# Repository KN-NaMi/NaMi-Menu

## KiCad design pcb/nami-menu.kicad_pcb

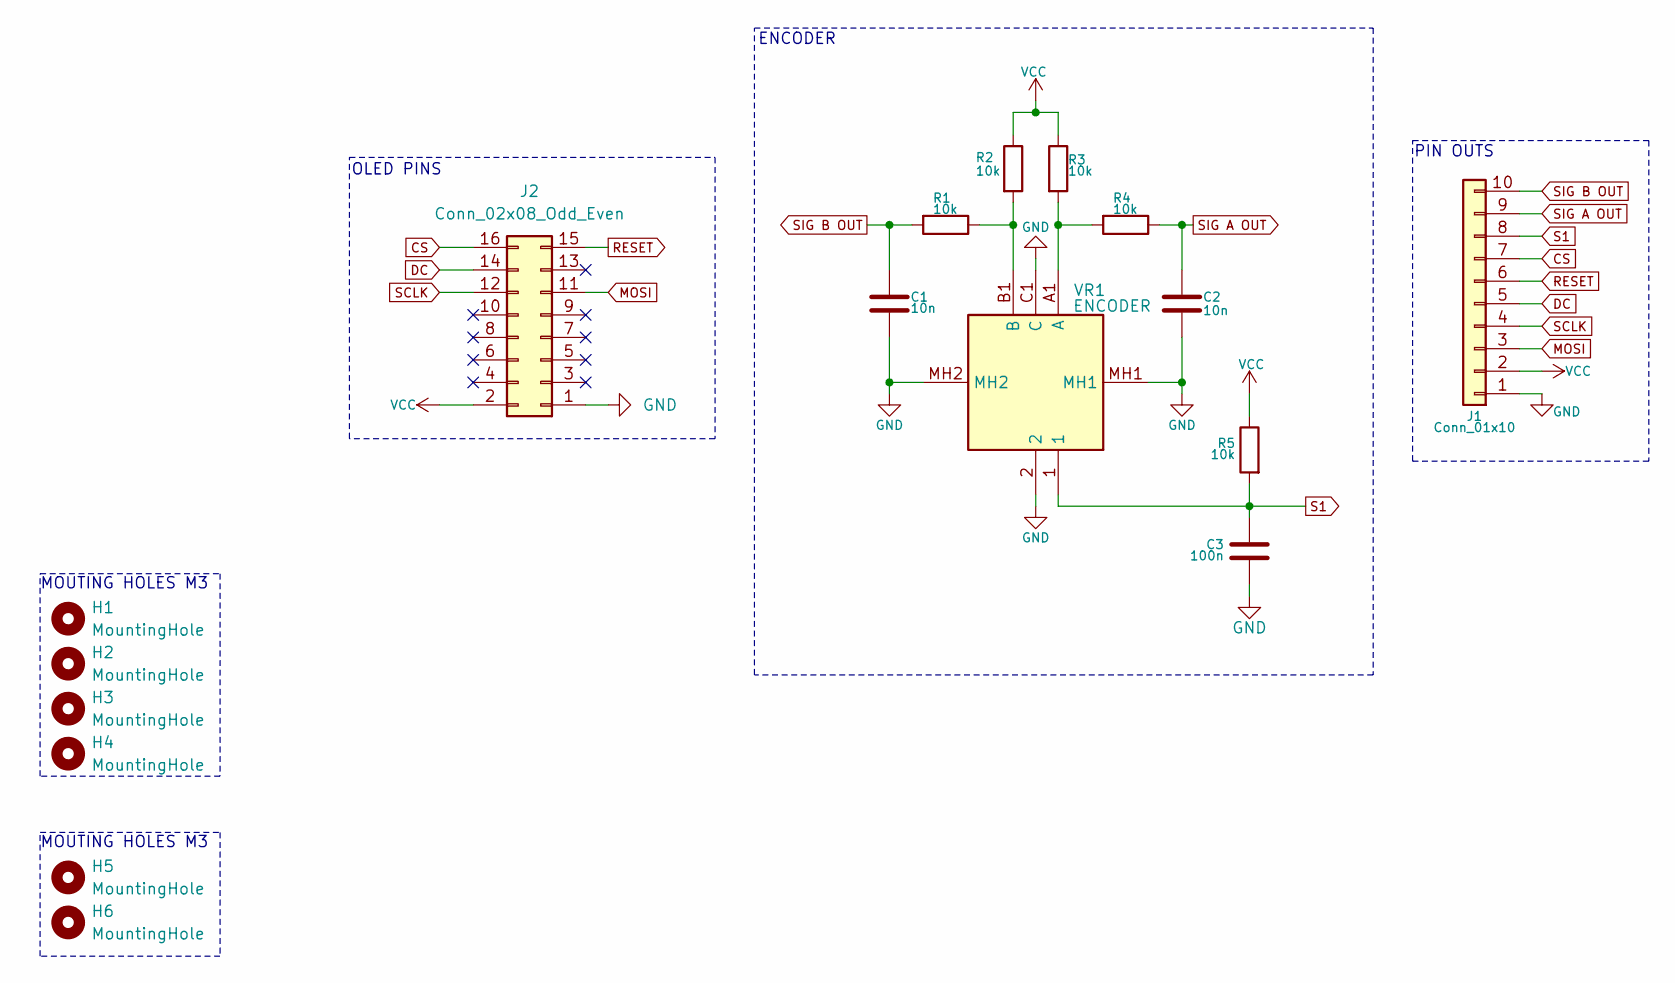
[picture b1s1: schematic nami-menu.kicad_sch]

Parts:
C1, C2: 10n; C_0402_1005Metric
C3: 100n; C_0402_1005Metric
H1, H2, H3, H4, H5, H6: MountingHole; MountingHole_3.2mm_M3
J1: Conn_01x10; PinHeader_1x10_P2.00mm_Vertical
J2: Conn_02x08_Odd_Even; PinSocket_2x08_P2.54mm_Vertical
R1, R2, R3, R4, R5: 10k; R_0402_1005Metric
VR1: ENCODER; PEC11R4220FS0024; Mouser Part Number 652-PEC11R-4220F-S24

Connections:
CS: J1.7, J2.16
DC: J1.5, J2.14
GND: C1.2, C2.2, C3.2, J1.1, J2.1, VR1.2, VR1.C1 (C), VR1.MH1, VR1.MH2
MOSI: J1.3, J2.11
unnamed: R3.2, R4.2, VR1.A1 (A)
unnamed: R1.1, R2.2, VR1.B1 (B)
RESET: J1.6, J2.15
S1: C3.1, J1.8, R5.2, VR1.1
SCLK: J1.4, J2.12
SIG A OUT: C2.1, J1.9, R4.1
SIG B OUT: C1.1, J1.10, R1.2
VCC: J1.2, J2.2, R2.1, R3.1, R5.1

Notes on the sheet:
OLED PINS
MOUTING HOLES M3
PIN OUTS
ENCODER

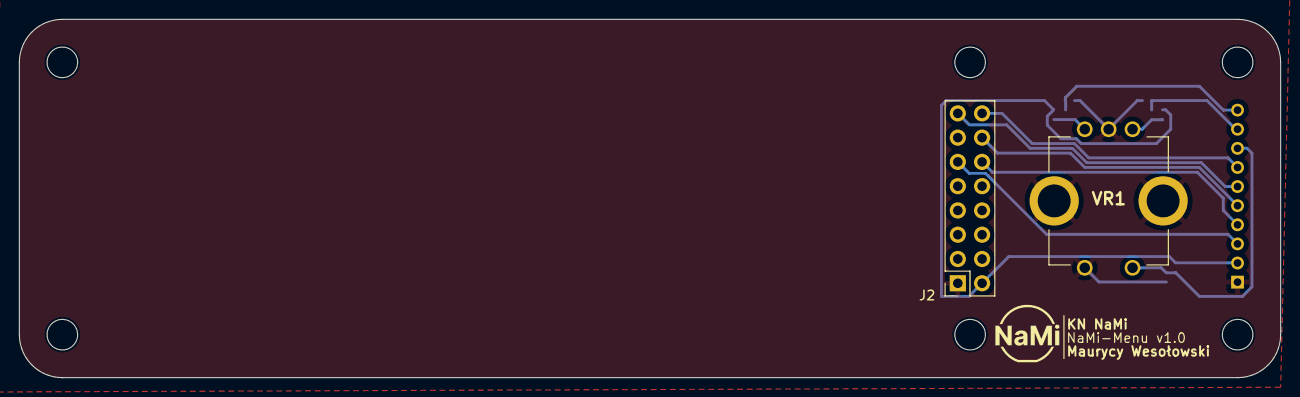
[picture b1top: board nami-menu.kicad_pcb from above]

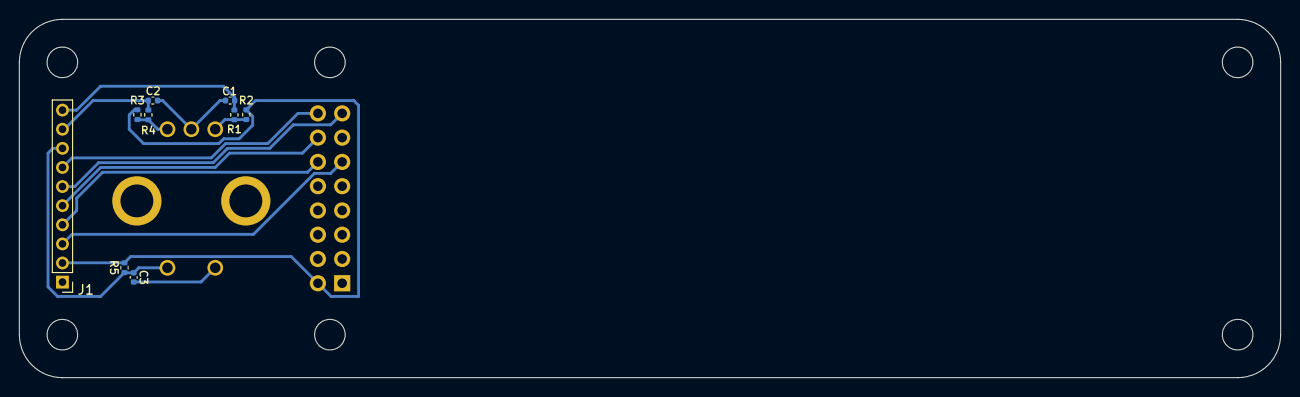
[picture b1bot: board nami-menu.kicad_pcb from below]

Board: 2 copper layers, 132.0 x 37.5 mm, 17 parts (9 on the bottom side), 12 nets.

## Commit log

2025-03-30 init commit
2025-03-30 OLED_Encoder
2025-03-30 refactor
2025-03-31 rename pcb
